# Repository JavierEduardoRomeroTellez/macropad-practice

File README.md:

# macropad-practice
 Making a 5 keys and encoder macropad

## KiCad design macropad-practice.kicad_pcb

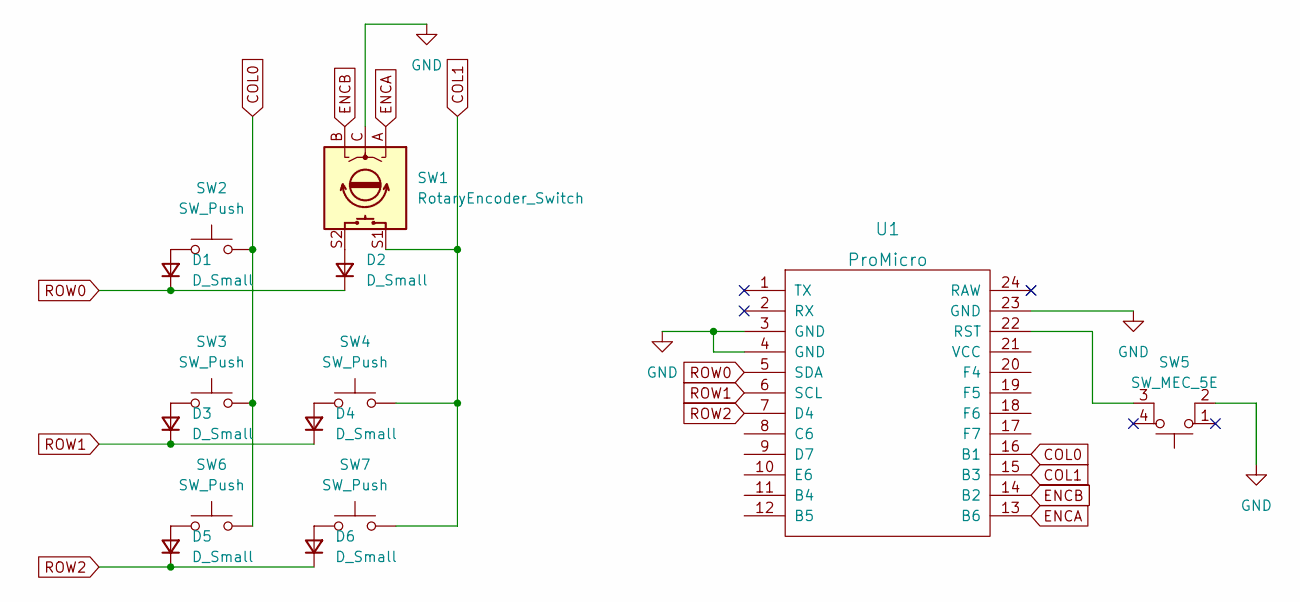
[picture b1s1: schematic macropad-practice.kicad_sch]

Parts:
D1, D2, D3, D4, D5, D6: D_Small; D_SOD-123
SW1: RotaryEncoder_Switch; RotaryEncoder_Alps_EC11E-Switch_Vertical_H20mm
SW2, SW3, SW4, SW6, SW7: SW_Push; MX-1U-NoLED
SW5: SW_MEC_5E; PushButton_6x6mm_TH
U1: ProMicro

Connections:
COL0: SW2.2, SW3.2, SW6.2, U1.16 (B1)
COL1: SW1.S1, SW4.2, SW7.2, U1.15 (B3)
ENCA: SW1.A, U1.13 (B6)
ENCB: SW1.B, U1.14 (B2)
GND: SW1.C, SW5.2, U1.3 (GND), U1.4 (GND), U1.23 (GND)
unnamed: D1.2 (A), SW2.1
unnamed: D2.2 (A), SW1.S2
unnamed: D3.2 (A), SW3.1
unnamed: D4.2 (A), SW4.1
unnamed: D5.2 (A), SW6.1
unnamed: D6.2 (A), SW7.1
unnamed: SW5.3 (K), U1.22 (RST)
ROW0: D1.1 (K), D2.1 (K), U1.5 (SDA)
ROW1: D3.1 (K), D4.1 (K), U1.6 (SCL)
ROW2: D5.1 (K), D6.1 (K), U1.7 (D4)

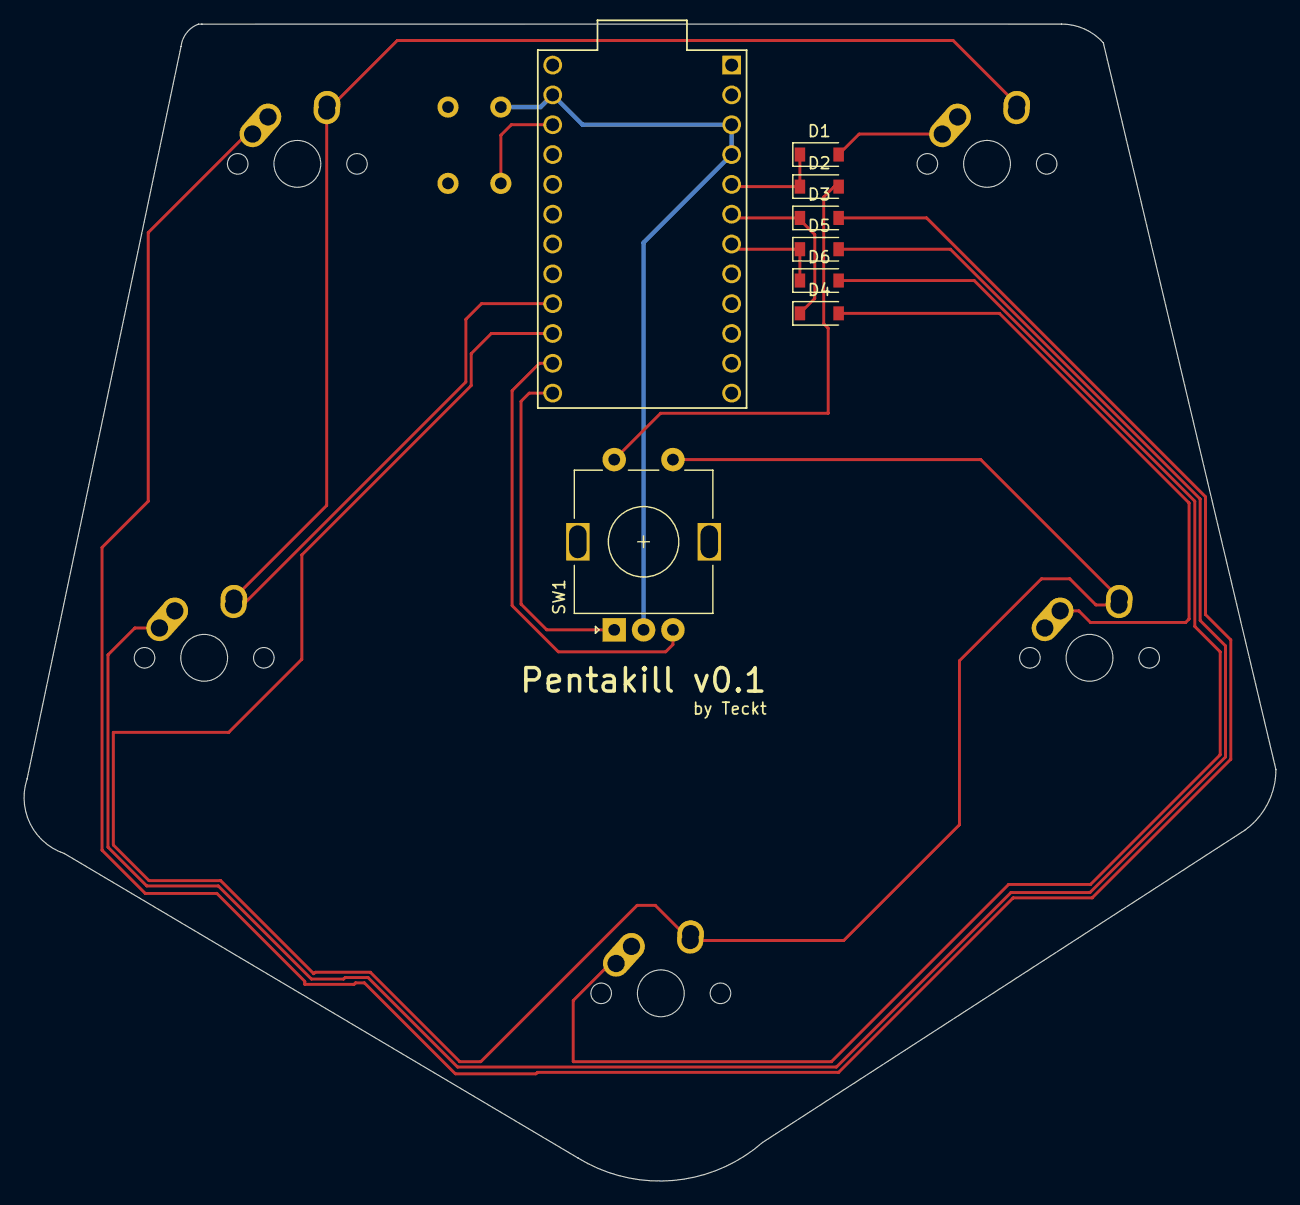
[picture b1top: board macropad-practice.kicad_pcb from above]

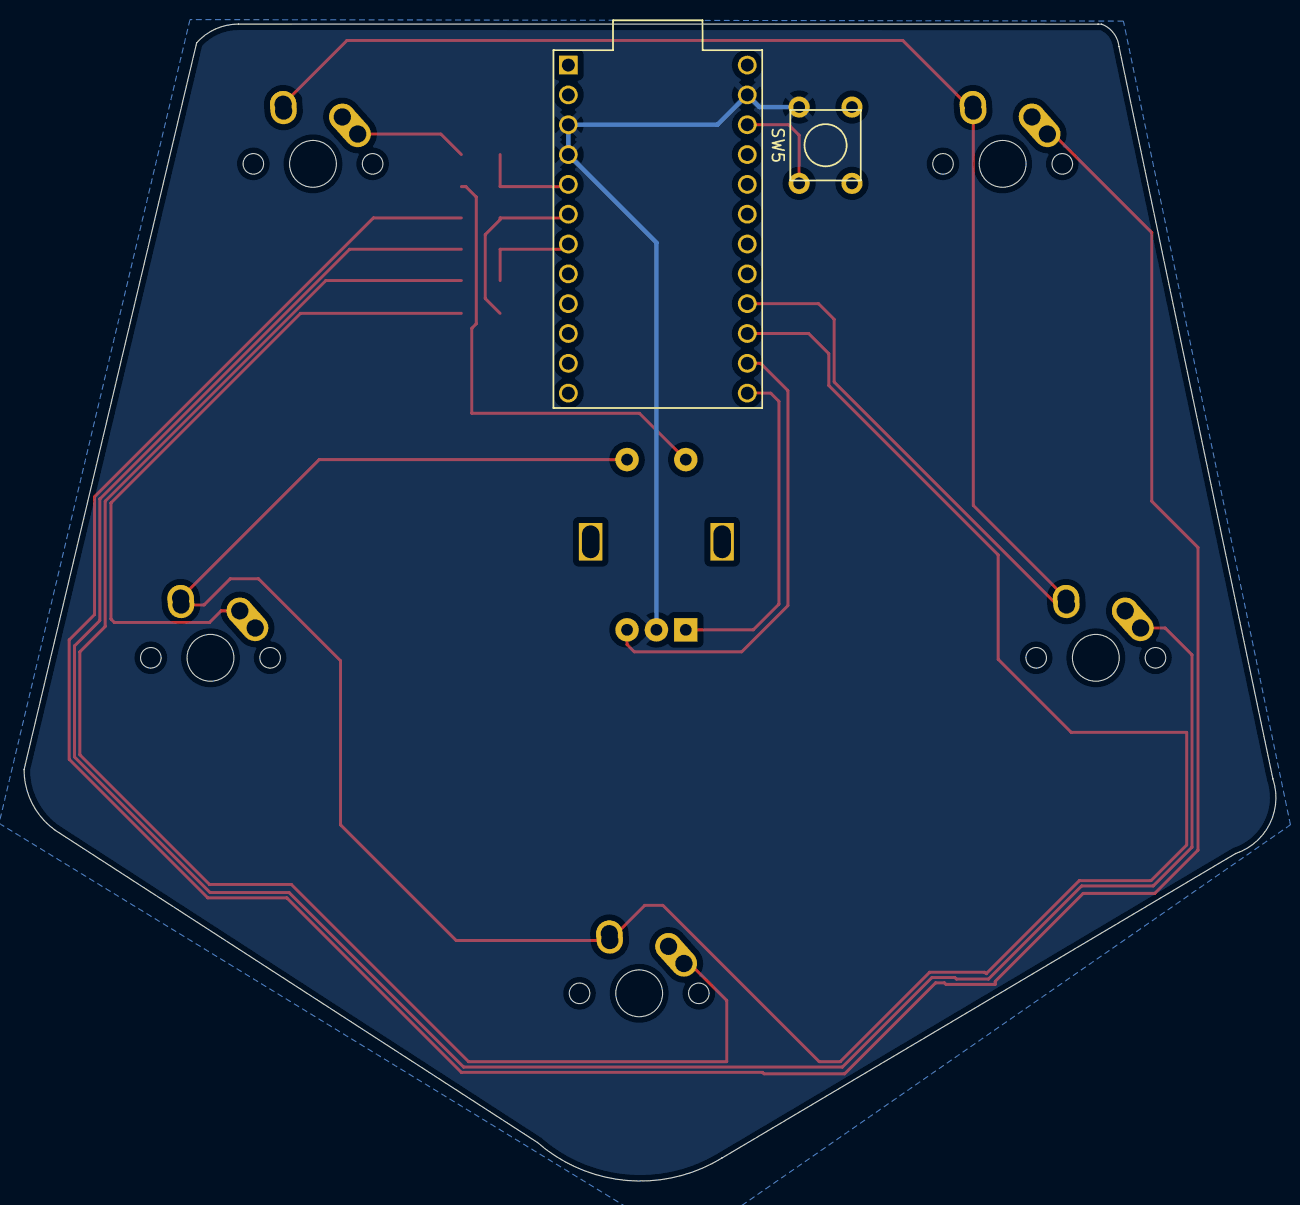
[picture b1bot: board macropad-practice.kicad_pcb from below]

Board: 2 copper layers, 106.6 x 98.5 mm, 14 parts (2 on the bottom side), 15 nets.

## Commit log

2022-05-17 Base project created
2022-05-18 Made the matrix and reset button
2022-05-18 Footprints assigned
2022-05-18 routing done
2022-05-18 added some details
